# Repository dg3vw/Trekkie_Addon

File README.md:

# Trekkie_Addon - USS Enterprise SAO

my contribution to Hackaday Europe 2025 Badge SAO

## NCC-1701-D - USS Enterprise 

### general 
* hardware compatible to 2024 Supercon 8 I2C prototyping petal SAO, using CH32v003 (see: https://github.com/Hack-a-Day/2024-Supercon-8-Add-On-Badge/tree/main/hardware/sao/i2c_proto_petal#prototyping-i2c-sao-petal-for-supercon-8)
* I added a few leds, two switches and a buzzer. Every LED is connected to a single gpio pin.
* you can change the light and sound as you wish, also with the PIpico on the badge

if u use my firmware, dont fire to much ;-)

### PINOUT: 
* PC0 - buzzer
* PC3 - front dish top led
* PC4 - engine nacelles left back
* PC5 - engine nacelles back
* PC6 - engine nacelles front
* PC7 - engine nacelles front
* PD0 - deflecor led
* PD1 - programming pin. connected to SAO connector pin 2
* PD2 - dish top left
* PD3 - dish top right
* PD4 - dish bottom left
* PD5 - dish bottom right
* PD6 - SWITCH 2 - fire the plasma cannon
* PD7 - SWITCH 1 - power up or reset (NRST), that can be changed to regular gpio using minichlink -D (from ch32fun)

## some impressions from the making:

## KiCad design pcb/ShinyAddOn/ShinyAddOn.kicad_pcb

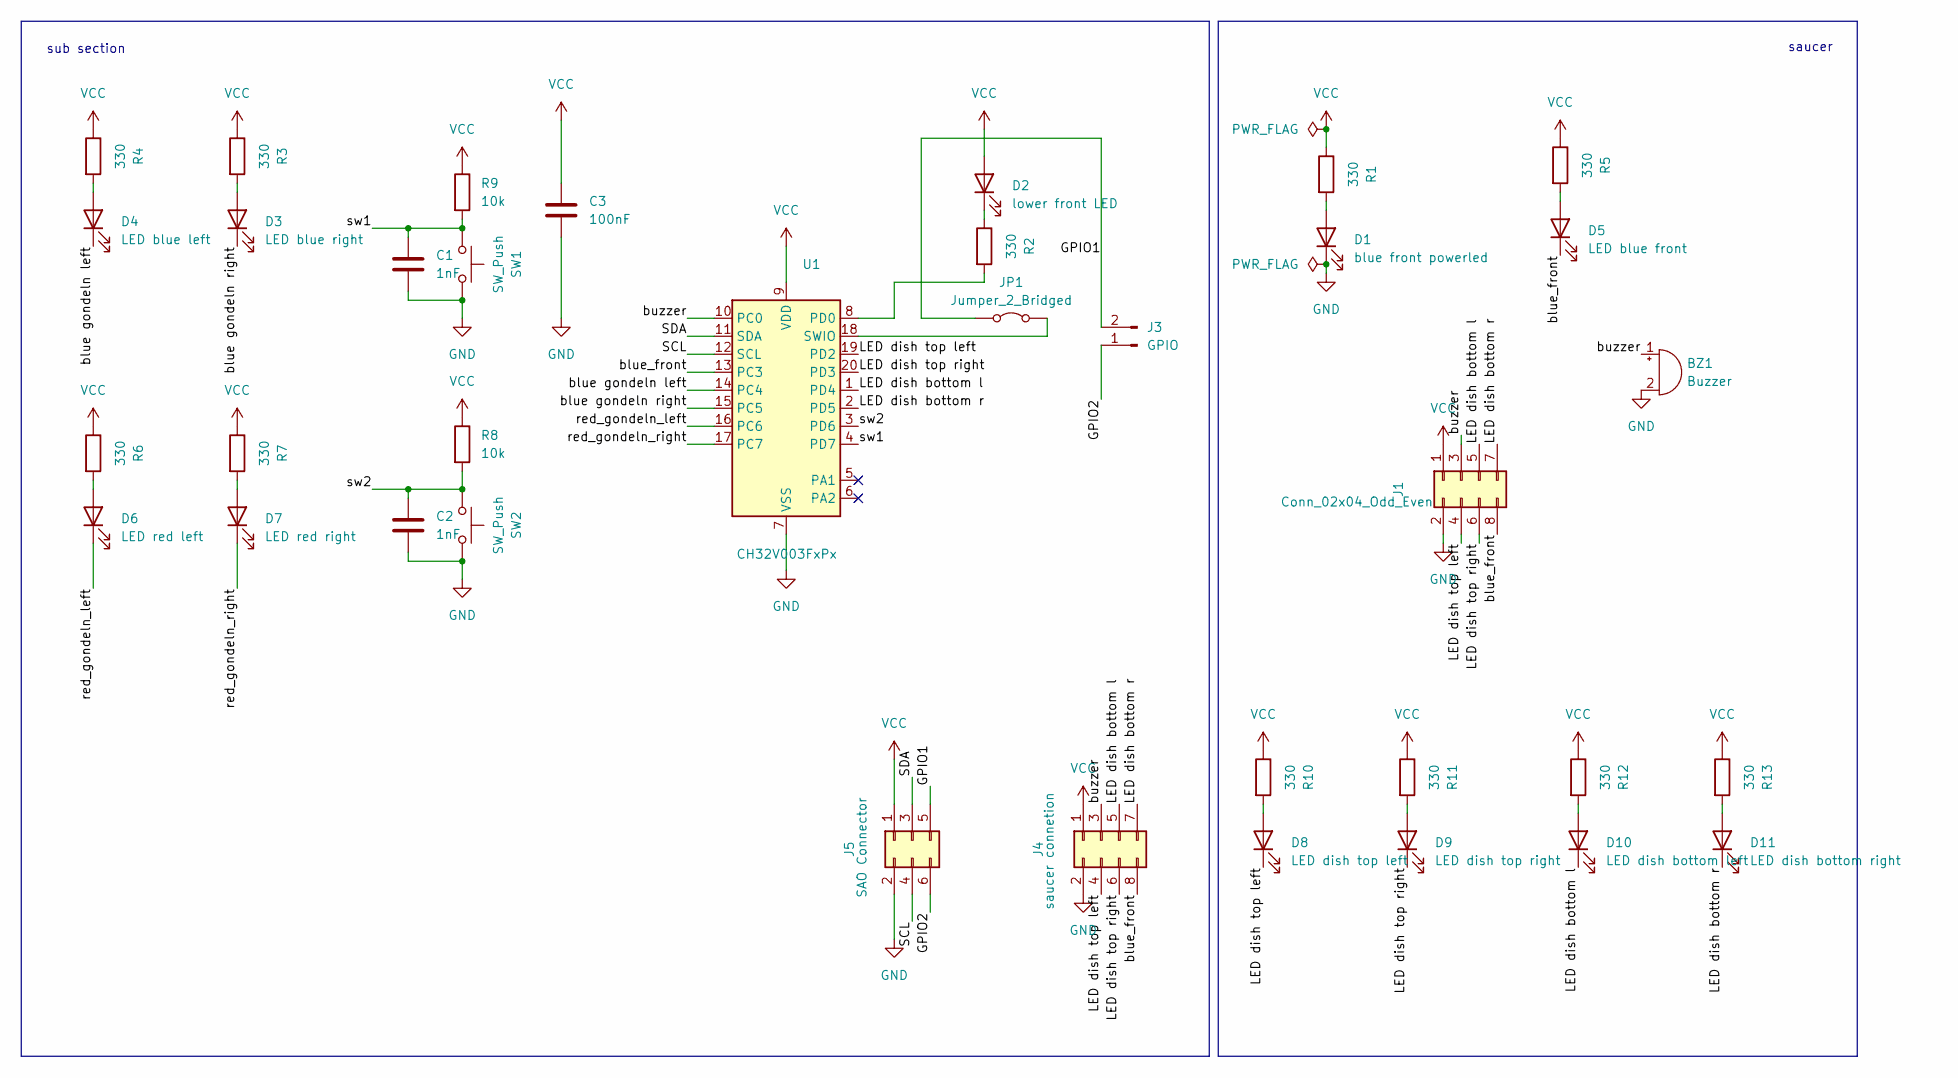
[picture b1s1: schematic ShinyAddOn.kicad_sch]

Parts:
BZ1: Buzzer; Buzzer_12x9.5RM7.6
C1, C2: 1nF; C_0603_1608Metric_Pad1.08x0.95mm_HandSolder
C3: 100nF; C_0603_1608Metric_Pad1.08x0.95mm_HandSolder
D1: blue front powerled; LED_0603_1608Metric_Pad1.05x0.95mm_HandSolder
D2: lower front LED; LED_0603_1608Metric_Pad1.05x0.95mm_HandSolder
D3: LED blue right; LED_0603_1608Metric_Pad1.05x0.95mm_HandSolder
D4: LED blue left; LED_0603_1608Metric_Pad1.05x0.95mm_HandSolder
D5: LED blue front; LED_0603_1608Metric_Pad1.05x0.95mm_HandSolder
D6: LED red left; LED_0603_1608Metric_Pad1.05x0.95mm_HandSolder
D7: LED red right; LED_0603_1608Metric_Pad1.05x0.95mm_HandSolder
D8: LED dish top left; LED_0603_1608Metric_Pad1.05x0.95mm_HandSolder
D9: LED dish top right; LED_0603_1608Metric_Pad1.05x0.95mm_HandSolder
D10: LED dish bottom left; LED_0603_1608Metric_Pad1.05x0.95mm_HandSolder
D11: LED dish bottom right; LED_0603_1608Metric_Pad1.05x0.95mm_HandSolder
J1: Conn_02x04_Odd_Even; PinHeader_2x04_P2.54mm_Vertical
J3: GPIO; SolderJumper-2_P1.3mm_Open_RoundedPad1.0x1.5mm
J4: saucer connetion; PinSocket_2x04_P2.54mm_Vertical
J5: SAO Connector; PinHeader_2x03_P2.54mm_Vertical
JP1: Jumper_2_Bridged; SolderJumper-2_P1.3mm_Bridged_RoundedPad1.0x1.5mm
R1, R2, R3, R4, R5, R6, R7, R10, R11, R12, R13: 330; R_0603_1608Metric_Pad0.98x0.95mm_HandSolder
R8, R9: 10k; R_0603_1608Metric_Pad0.98x0.95mm_HandSolder
SW1, SW2: SW_Push; SW_Tactile_SPST_NO_Straight_CK_PTS636Sx25SMTRLFS
U1: CH32V003FxPx; TSSOP-20_4.4x6.5mm_P0.65mm

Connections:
/GPIO1: J3.2, J5.5, JP1.1 (A)
/GPIO2: J3.1, J5.6
/LED dish bottom l: D10.1 (K), J1.5, J4.5, U1.1 (PD4)
/LED dish bottom r: D11.1 (K), J1.7, J4.7, U1.2 (PD5)
/LED dish top left: D8.1 (K), J1.4, J4.4, U1.19 (PD2)
/LED dish top right: D9.1 (K), J1.6, J4.6, U1.20 (PD3)
/SCL: J5.4, U1.12 (SCL)
/SDA: J5.3, U1.11 (SDA)
/blue gondeln left: D4.1 (K), U1.14 (PC4)
/blue gondeln right: D3.1 (K), U1.15 (PC5)
/blue_front: D5.1 (K), J1.8, J4.8, U1.13 (PC3)
/buzzer: BZ1.1 (+), J1.3, J4.3, U1.10 (PC0)
/red_gondeln_left: D6.1 (K), U1.16 (PC6)
/red_gondeln_right: D7.1 (K), U1.17 (PC7)
/sw1: C1.1, R9.2, SW1.1, U1.4 (PD7)
/sw2: C2.1, R8.2, SW2.1, U1.3 (PD6)
GND: BZ1.2 (-), C1.2, C2.2, C3.2, D1.1 (K), J1.2, J4.2, J5.2, SW1.2, SW2.2, U1.7 (VSS)
unnamed: D1.2 (A), R1.2
unnamed: D2.1 (K), R2.1
unnamed: D3.2 (A), R3.2
unnamed: D4.2 (A), R4.2
unnamed: D5.2 (A), R5.2
unnamed: D6.2 (A), R6.2
unnamed: D7.2 (A), R7.2
unnamed: D8.2 (A), R10.2
unnamed: D9.2 (A), R11.2
unnamed: D10.2 (A), R12.2
unnamed: D11.2 (A), R13.2
unnamed: JP1.2 (B), U1.18 (SWIO)
unnamed: R2.2, U1.8 (PD0)
VCC: C3.1, D2.2 (A), J1.1, J4.1, J5.1, R1.1, R3.1, R4.1, R5.1, R6.1, R7.1, R8.1, R9.1, R10.1, R11.1, R12.1, R13.1, U1.9 (VDD)

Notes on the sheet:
saucer
sub section

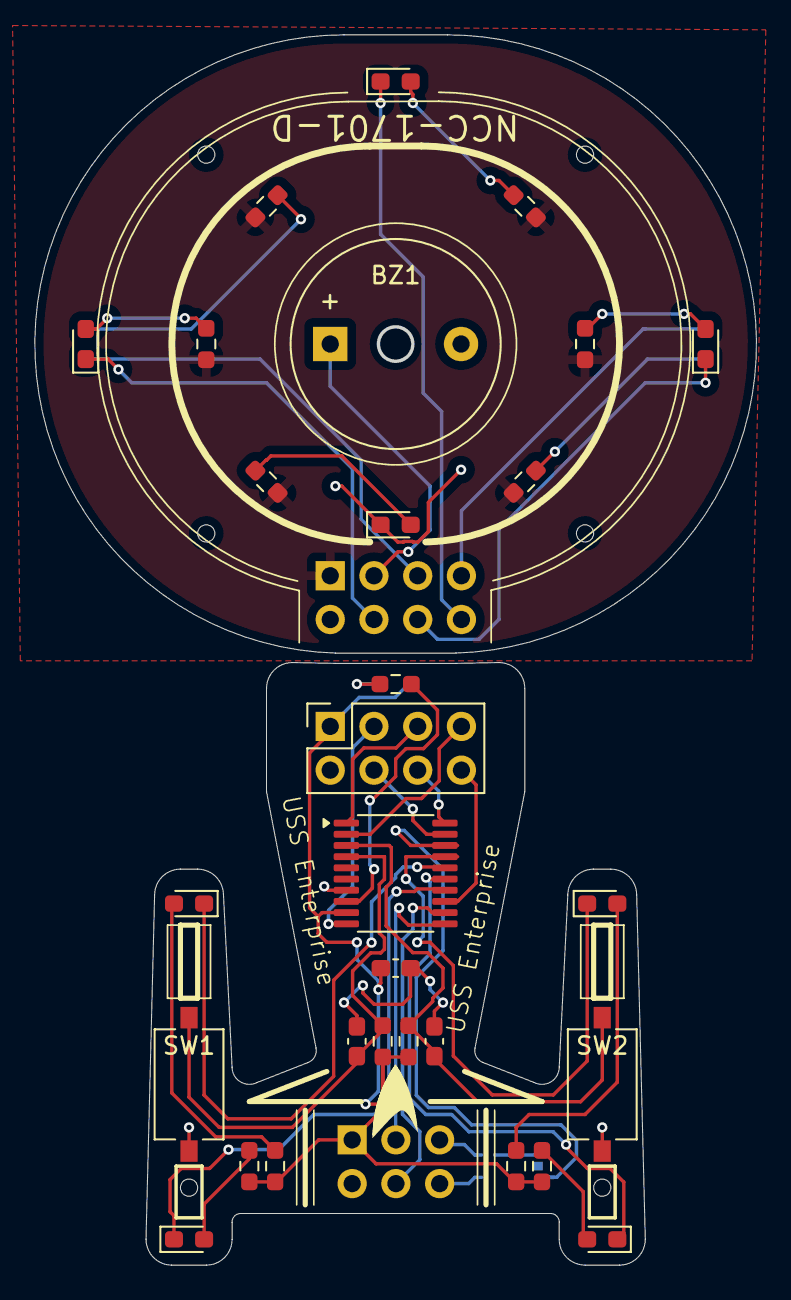
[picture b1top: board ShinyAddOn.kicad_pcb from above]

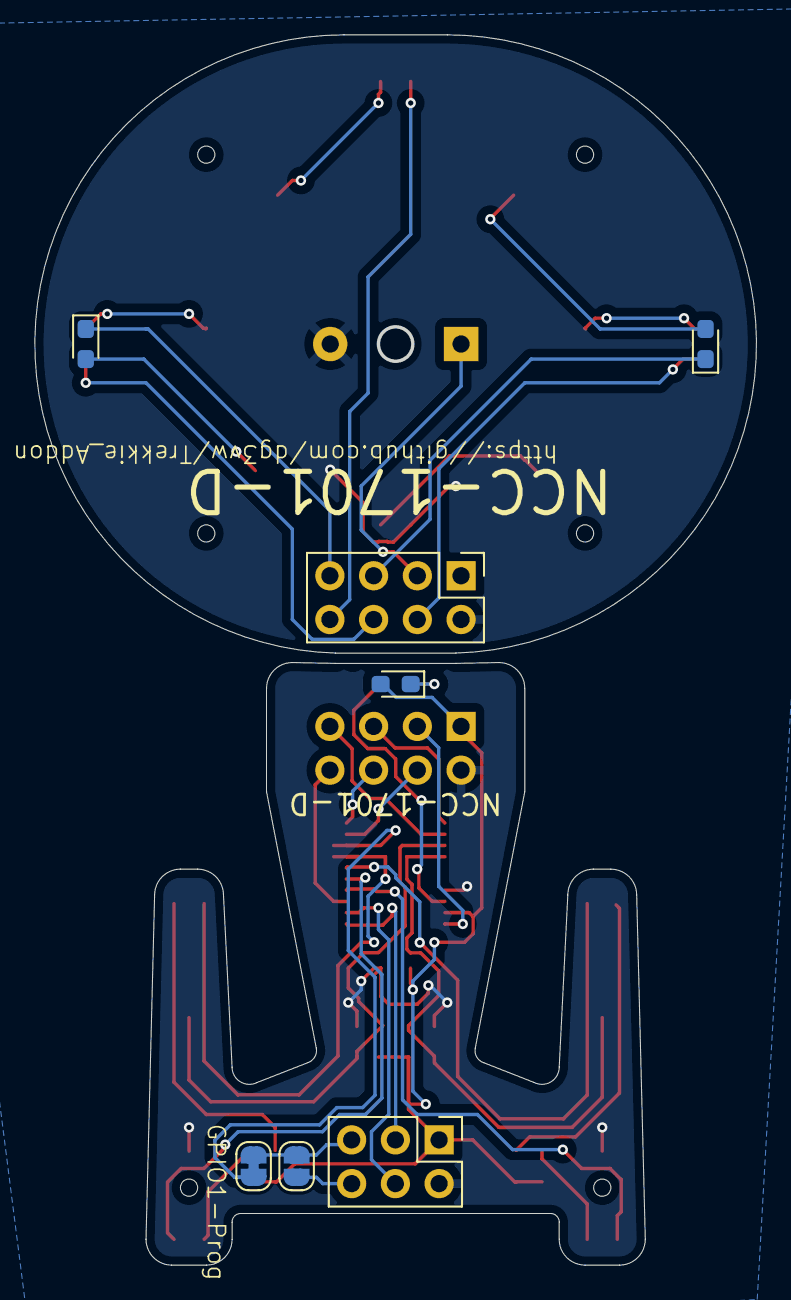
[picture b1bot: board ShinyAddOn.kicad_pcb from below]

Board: 2 copper layers, 41.8 x 71.3 mm, 36 parts (7 on the bottom side), 31 nets.

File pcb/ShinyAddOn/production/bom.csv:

Designator,Footprint,Quantity,Value,LCSC Part #
BZ1,Buzzer_12x9.5RM7.6,1,Buzzer,
"C1, C2",0603,2,1nF,
C3,0603,1,100nF,
D1,0603,1,blue front powerled,
D10,0603,1,LED dish bottom left,
D11,0603,1,LED dish bottom right,
D2,0603,1,lower front LED,
D3,0603,1,LED blue right,
D4,0603,1,LED blue left,
D5,0603,1,LED blue front,
D6,0603,1,LED red left,
D7,0603,1,LED red right,
D8,0603,1,LED dish top left,
D9,0603,1,LED dish top right,
J1,PinHeader_2x04_P2.54mm_Vertical,1,Conn_02x04_Odd_Even,
J3,SolderJumper-2_P1.3mm_Open_RoundedPad1.0x1.5mm,1,GPIO,
J4,PinSocket_2x04_P2.54mm_Vertical,1,saucer connetion,
J5,PinHeader_2x03_P2.54mm_Vertical,1,SAO Connector,
JP1,SolderJumper-2_P1.3mm_Bridged_RoundedPad1.0x1.5mm,1,Jumper_2_Bridged,
"R1, R10, R11, R12, R13, R2, R3, R4, R5, R6, R7",0603,11,330,
"R8, R9",0603,2,10k,
"SW1, SW2",SW_Tactile_SPST_NO_Straight_CK_PTS636Sx25SMTRLFS,2,SW_Push,
U1,TSSOP-20_4.4x6.5mm_P0.65mm,1,CH32V003FxPx,

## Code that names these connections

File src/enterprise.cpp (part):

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#include <Arduino.h>

// Define LED pins
#define LED_FRONT PC3
#define BUZZER PC0
#define LED_BLUE_MOTOR_LEFT PC4
#define LED_BLUE_MOTOR_RIGHT PC5
#define LED_RED_MOTOR_LEFT PC6
#define LED_RED_MOTOR_RIGHT PC7
#define LED_DISH_TOP_LEFT PD2
#define LED_DISH_TOP_RIGHT PD3
#define LED_DISH_BOTTOM_LEFT PD4
#define LED_DISH_BOTTOM_RIGHT PD5
#define LED_DEFLECTOR PD0
#define SWITCH_1 PD6
#define SWITCH_2 PD7 // <- work only if Pin D7 is reprogrammed to be an input (not NRST)

// Structure to hold LED timing parameters
struct LedTiming {
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
void setup() {
    pinMode(LED_FRONT, OUTPUT);
    pinMode(BUZZER, OUTPUT);
    pinMode(LED_BLUE_MOTOR_LEFT, OUTPUT);
    pinMode(LED_BLUE_MOTOR_RIGHT, OUTPUT);
    pinMode(LED_RED_MOTOR_LEFT, OUTPUT);
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
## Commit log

2025-02-02 initial commit, pcb und platformio project data added
2025-02-16 worked on the pcb
2025-02-19 pcb updated
2025-03-06 panel tests
2025-03-10 testcode für alle funktionen
2025-03-13 changes on blinking sequence
2025-03-14 added some infos and pics
2025-03-14 add pics
